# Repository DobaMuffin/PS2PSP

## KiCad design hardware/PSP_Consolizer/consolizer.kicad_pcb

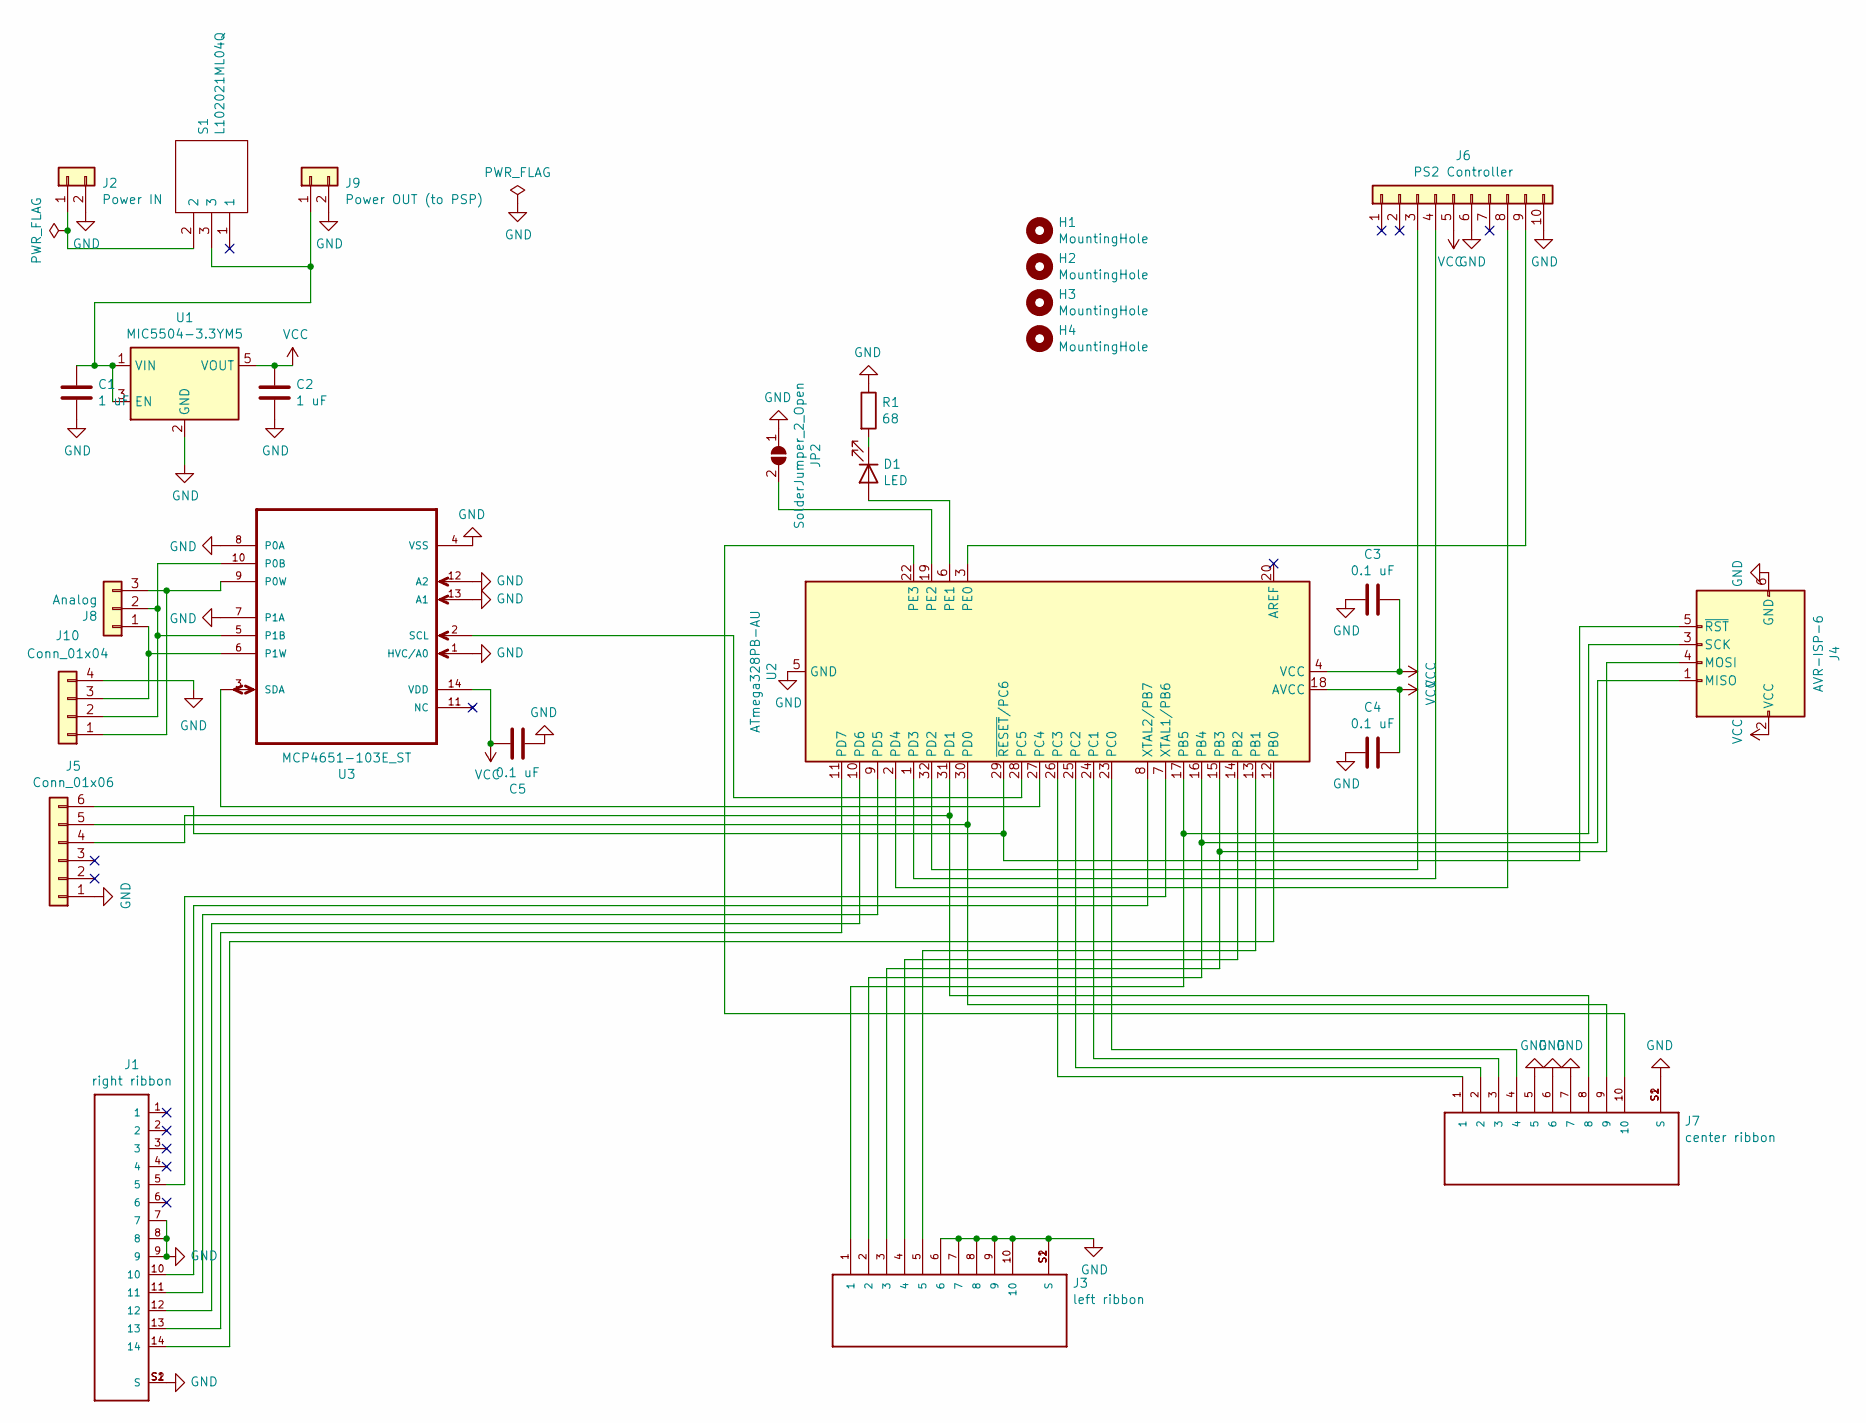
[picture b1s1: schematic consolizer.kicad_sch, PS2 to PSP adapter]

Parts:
C1, C2: 1 uF; C_0603_1608Metric_Pad1.05x0.95mm_HandSolder
C3, C4, C5: 0.1 uF; C_0603_1608Metric_Pad1.05x0.95mm_HandSolder
D1: LED; LED_0603_1608Metric_Pad1.05x0.95mm_HandSolder
H1, H2, H3, H4: MountingHole; MountingHole_2.2mm_M2
J1: right ribbon; TE_1-1734839-4_1x14-1MP_P0.5mm_Horizontal
J2: Power IN; PinHeader_1x02_P2.54mm_Vertical
J3: left ribbon; Left_Ribbon
J4: AVR-ISP-6; PinHeader_2x03_P2.54mm_Vertical
J5: Conn_01x06; PinHeader_1x06_P2.54mm_Horizontal
J6: PS2 Controller; ps2_connector
J7: center ribbon; TE_1-1734839-0_1x10-1MP_P0.5mm_Horizontal
J8: Analog; PinHeader_1x03_P2.54mm_Vertical
J9: Power OUT (to PSP); PinHeader_1x02_P2.54mm_Horizontal
J10: Conn_01x04; TE_0-1734839-45_1x04-1MP_P0.5mm_Horizontal
JP2: SolderJumper_2_Open; SolderJumper-2_P1.3mm_Open_RoundedPad1.0x1.5mm
R1: 68; R_0603_1608Metric_Pad1.05x0.95mm_HandSolder
S1: L102021ML04Q; Manufacturer_Part_Number L102021ML04Q; Mouser Part Number 611-L102021ML04Q
U1: MIC5504-3.3YM5; SOT-23-5
U2: ATmega328PB-AU; TQFP-32_7x7mm_P0.8mm
U3: MCP4651-103E_ST; TSSOP-14_4.4x5mm_P0.65mm

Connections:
GND: C1.2, C2.2, C3.1, C4.1, C5.2, J1.7, J1.8, J1.9, J1.MP, J1.S1 (S), J1.S2 (S), J2.2, J3.6, J3.7, J3.8, J3.9, J3.10, J3.MP, J3.S1 (S), J3.S2 (S), J4.6 (GND), J5.1, J6.6, J6.10, J7.5, J7.6, J7.7, J7.MP, J7.S1 (S), J7.S2 (S), J9.2, J10.4, J10.MP, JP2.1 (A), R1.1, U1.2 (GND), U2.5 (GND), U2.21 (GND), U3.1 (HVC/A0), U3.4 (VSS), U3.7 (P1A), U3.8 (P0A), U3.12 (A2), U3.13 (A1)
unnamed: C1.1, J9.1, S1.3, U1.1 (VIN), U1.3 (EN)
unnamed: D1.1 (K), R1.2
unnamed: D1.2 (A), U2.6 (PE1)
unnamed: J1.5, U2.7 (XTAL1/PB6)
unnamed: J1.10, U2.8 (XTAL2/PB7)
unnamed: J1.11, U2.9 (PD5)
unnamed: J1.12, U2.10 (PD6)
unnamed: J1.13, U2.11 (PD7)
unnamed: J1.14, U2.12 (PB0)
unnamed: J2.1, S1.2
unnamed: J3.1, J4.3 (SCK), U2.17 (PB5)
unnamed: J3.2, J4.1 (MISO), U2.16 (PB4)
unnamed: J3.3, J4.4 (MOSI), U2.15 (PB3)
unnamed: J3.4, U2.14 (PB2)
unnamed: J3.5, U2.13 (PB1)
unnamed: J4.5 (~RST), J5.6, U2.29 (~RESET/PC6)
unnamed: J5.4, J7.8, U2.31 (PD1)
unnamed: J5.5, J7.9, U2.30 (PD0)
unnamed: J6.3, U2.32 (PD2)
unnamed: J6.4, U2.1 (PD3)
unnamed: J6.8, U2.2 (PD4)
unnamed: J6.9, U2.3 (PE0)
unnamed: J7.1, U2.26 (PC3)
unnamed: J7.2, U2.25 (PC2)
unnamed: J7.3, U2.24 (PC1)
unnamed: J7.4, U2.23 (PC0)
unnamed: J7.10, U2.22 (PE3)
unnamed: J8.1, J10.3, U3.6 (P1W)
unnamed: J8.2, J10.2, U3.5 (P1B), U3.10 (P0B)
unnamed: J8.3, J10.1, U3.9 (P0W)
unnamed: JP2.2 (B), U2.19 (PE2)
unnamed: U2.27 (PC4), U3.3 (SDA)
unnamed: U2.28 (PC5), U3.2 (SCL)
VCC: C2.1, C3.2, C4.2, C5.1, J4.2 (VCC), J6.5, U1.5 (VOUT), U2.4 (VCC), U2.18 (AVCC), U3.14 (VDD)

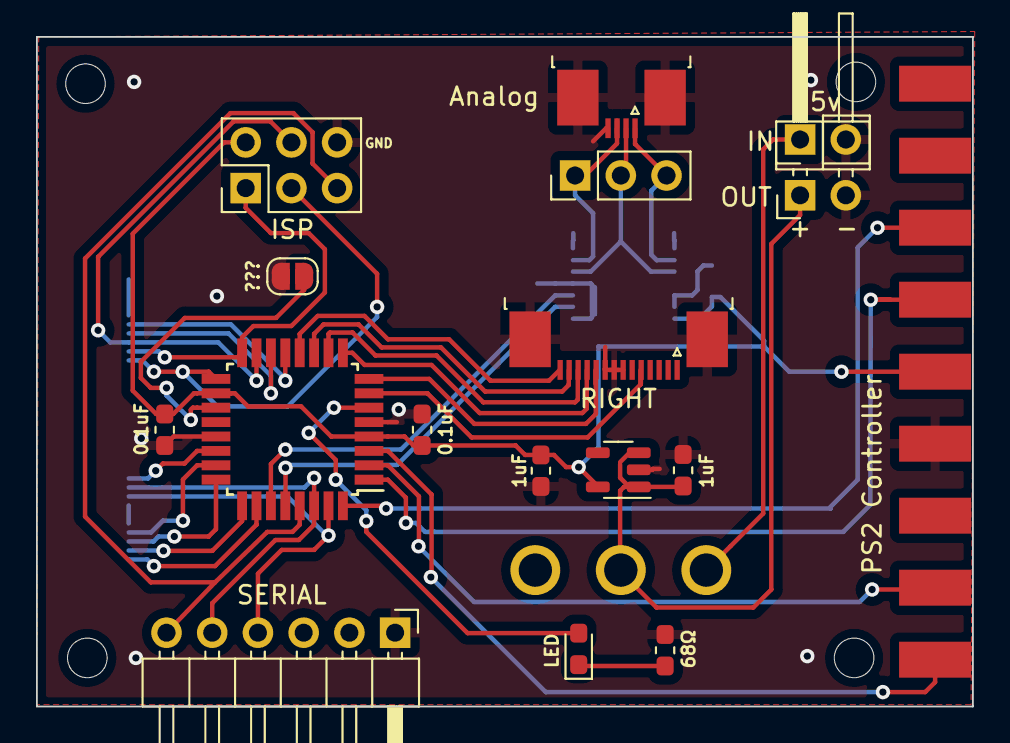
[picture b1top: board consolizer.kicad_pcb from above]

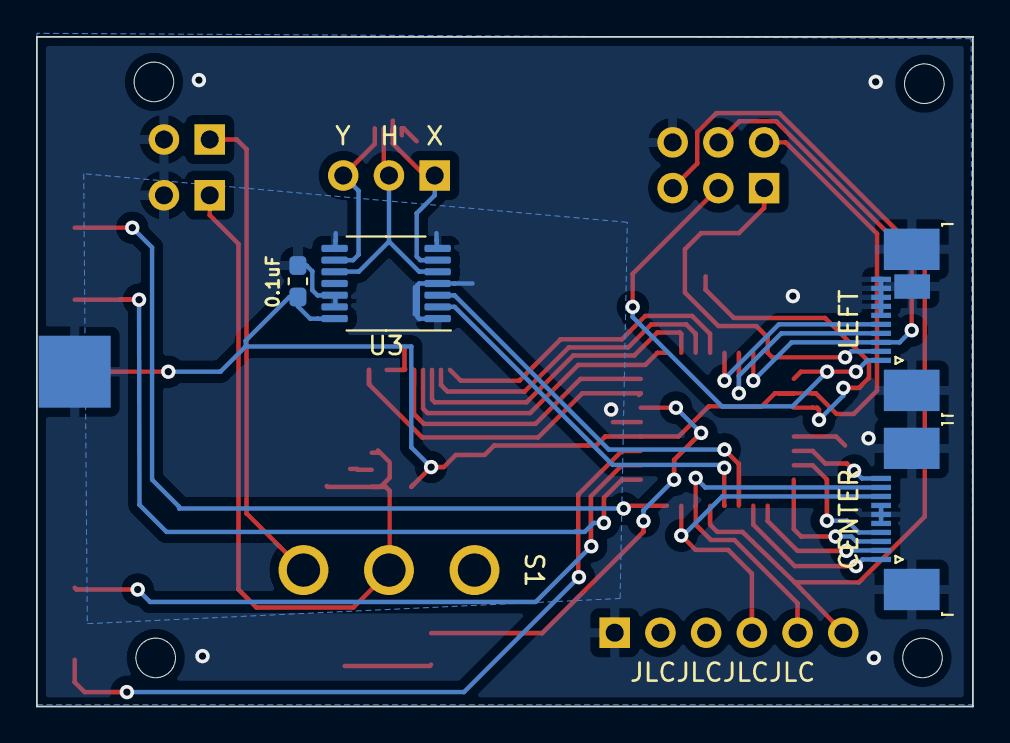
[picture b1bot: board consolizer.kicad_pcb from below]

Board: 2 copper layers, 52.0 x 37.2 mm, 26 parts (5 on the bottom side), 35 nets.

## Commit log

2022-09-26 Modified for PSP 3000 and added Gerber files for JLCPCB
2025-12-03 Modified project files
